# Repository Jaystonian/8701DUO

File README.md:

# 8701DUO
MOS8701 replacement module with a jumper to select NTSC or PAL having a dual-clock.

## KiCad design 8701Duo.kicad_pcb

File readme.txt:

Tested early August 2020.  Works great.  Needed to reverse the clock chips, corrected all files.  
NTSC standard clock should be next to the 3-SIP pin header.

PARTS
=====================
IDT 525-01RILFT (or 525-02R etc)
SN74LVC1G06DBVR (or 1g04, or 1g14, hct, ahct etc)
LFSPXO020648 (17.734MHz)
LFSPXO021772 (14.318MHz)          
2x 10nF 0805/2012 (for ics525)
2x 100nF 0805/2012 (for clocks & gate)
1x 20pF 0805/2012 
1x 8k2 0805/2012 (as pullup resistor)

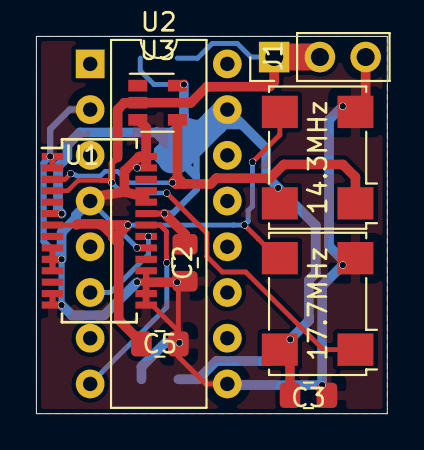
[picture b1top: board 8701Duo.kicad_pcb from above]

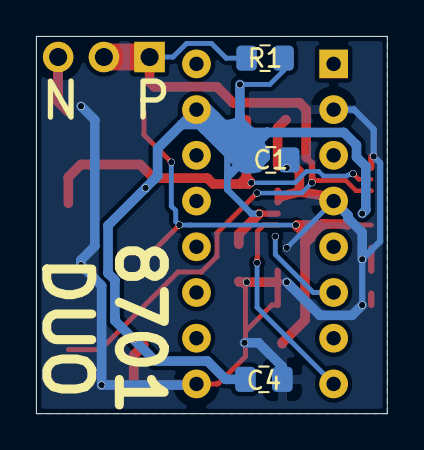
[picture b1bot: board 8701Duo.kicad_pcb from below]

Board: 2 copper layers, 19.5 x 21.0 mm, 12 parts (3 on the bottom side), 7 nets.

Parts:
14.3MHz: LFSPXO021772Bulk; Oscillator_SMD_IQD_IQXO70-4Pin_7.5x5.0mm
17.7MHz: LFSPXO020648Bulk; Oscillator_SMD_IQD_IQXO70-4Pin_7.5x5.0mm
C1, C2: 10n; C_0805_2012Metric_Pad1.15x1.40mm_HandSolder
C3, C4: 100n; C_0805_2012Metric_Pad1.15x1.40mm_HandSolder
C5: 15p-45p; C_0805_2012Metric_Pad1.15x1.40mm_HandSolder
J1: Clock; PinHeader_1x03_P2.54mm_Vertical
R1: 5k6; R_0805_2012Metric_Pad1.15x1.40mm_HandSolder
U1: ICS525-01R; SSOP-28_3.9x9.9mm_P0.635mm
U2: MOS8701; DIP-16_W7.62mm
U3: 74LVC1G06; SOT-23-5

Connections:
+5V: 14.3MHz.4, 17.7MHz.4, C1.1, C2.1, C3.2, C4.2, R1.1, U1.6, U1.23, U2.15, U3.5
GND: 14.3MHz.2, 17.7MHz.2, C1.2, C2.2, C3.1, C4.1, C5.2, J1.3, U1.1, U1.2, U1.9, U1.10, U1.11, U1.13, U1.14, U1.15, U1.16, U1.17, U1.18, U1.20, U1.24, U1.25, U1.27, U1.28, U2.2, U2.4, U2.9, U3.3
unnamed: 14.3MHz.3, 17.7MHz.3, C5.1, U1.7
unnamed: 14.3MHz.1, J1.1, J1.2, R1.2, U1.4, U3.2
unnamed: 17.7MHz.1, U1.3, U3.4
unnamed: U1.21, U2.6
unnamed: U1.22, U2.8

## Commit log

2020-06-22 Untested. Will update to confirm working.
2020-06-22 Appearance
2020-08-23 works great
